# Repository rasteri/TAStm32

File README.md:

# TAStm32
Please see the "Projects" section for an overview of the current status of this project!

Please see the "Wiki" section for the technical details of the serial communication protocol!

### Overview

This project aims to create an easy-to-use, multi-system TAS replay device to be used on actual consoles. The name of this project comes from the fact that it is powered by a STM32F4 microcontroller.

### Prerequisites

First clone or download this repository

#### Get Python3!
Install the [latest Python 3 release](https://www.python.org/downloads/)

(You may need to log out/log in to refresh the PATH variable)

Then install the required python modules with the following command:

    python3 -m pip install -r python/requirements.txt
    
#### Linux users -- make sure you are in the dialout and plugdev groups!
    
### Compilation

#### Linux
    apt install gcc-arm-none-eabi binutils-arm-none-eabi libnewlib-arm-none-eabi
OR the equivalent in your distribution

    make

#### Windows

1. Right-click on the project > Build Configurations > Set Active > Release.
1. Project > Build Project and check that the console shows no errors. The last line before "build finished" should be "arm-atollic-eabi-objcopy -O ihex TAStm32.elf TAStm32.hex".

### Flashing the firmware

#### Linux
    apt install dfu-util
OR the equivalent in your distribution

    make flash

#### Windows
1. Install Atollic TrueStudio
1. Install STM32CubeProgrammer
1. Open up the command prompt
1. Run setenv.bat included in the root directory
1. Run update.bat included in the root directory

### Usage

Dumped TAS movies are available in the [TASBot projects repo](https://github.com/dwangoac/TASBot-Projects/tree/master/replayfiles)

[Scripts to dump your own TASes](https://github.com/dwangoac/TASBot-Projects/blob/master/Dump_Scripts/)

Once you've prepared a movie dump, use it with the TAStm32. Here is one example example is here:

    python3 tastm32.py --console snes --players 1,5 --dpcm --clock 14 --transition 2123 A --blank 1 smb3_agdq.r16m

### Special Thanks
#### TheMas3212 - The main contributor to this project. Aided with all things python, designing the serial communication protocol, helping with PCB design, and debugging throughout the whole process.
#### CraftedCart - Designed the awesome-looking 3D case
#### total (@tewtal) - Helped with NES/SNES protocol and debugging. Provided his code as a reference
#### booto (@booto) - Helped fix N64/GC protocols, serial-over-USB, and debugging

dwangoAC (@dwangoac) - warmly accepting me into the TASBot community

micro500 (@micro500) - spent a lot of time teaching me how console replay devices work at a low level

true - for teaching me hardware concepts, helping me choose the perfect MCU for the job, and explaining a lot of low-level things to me

Tien Majerle (@MaJerle) - the owner of https://stm32f4-discovery.net/ helped me with the function which jumps to the DFU bootloader code

Ilari - for being an extraordinary wealth of knowledge on most topics

Serisium (@serisium) - helped with debugging and PCB design

rcombs (@rcombs) - helped with optimizing the N64 protocol

Sauraen (@sauraen) - Linux setup and installation notes

Derf - worked on debugging the genesis protocol together

#### If I accidentally forgot to credit you, please let me know so I can fix it!

 - Ownasaurus

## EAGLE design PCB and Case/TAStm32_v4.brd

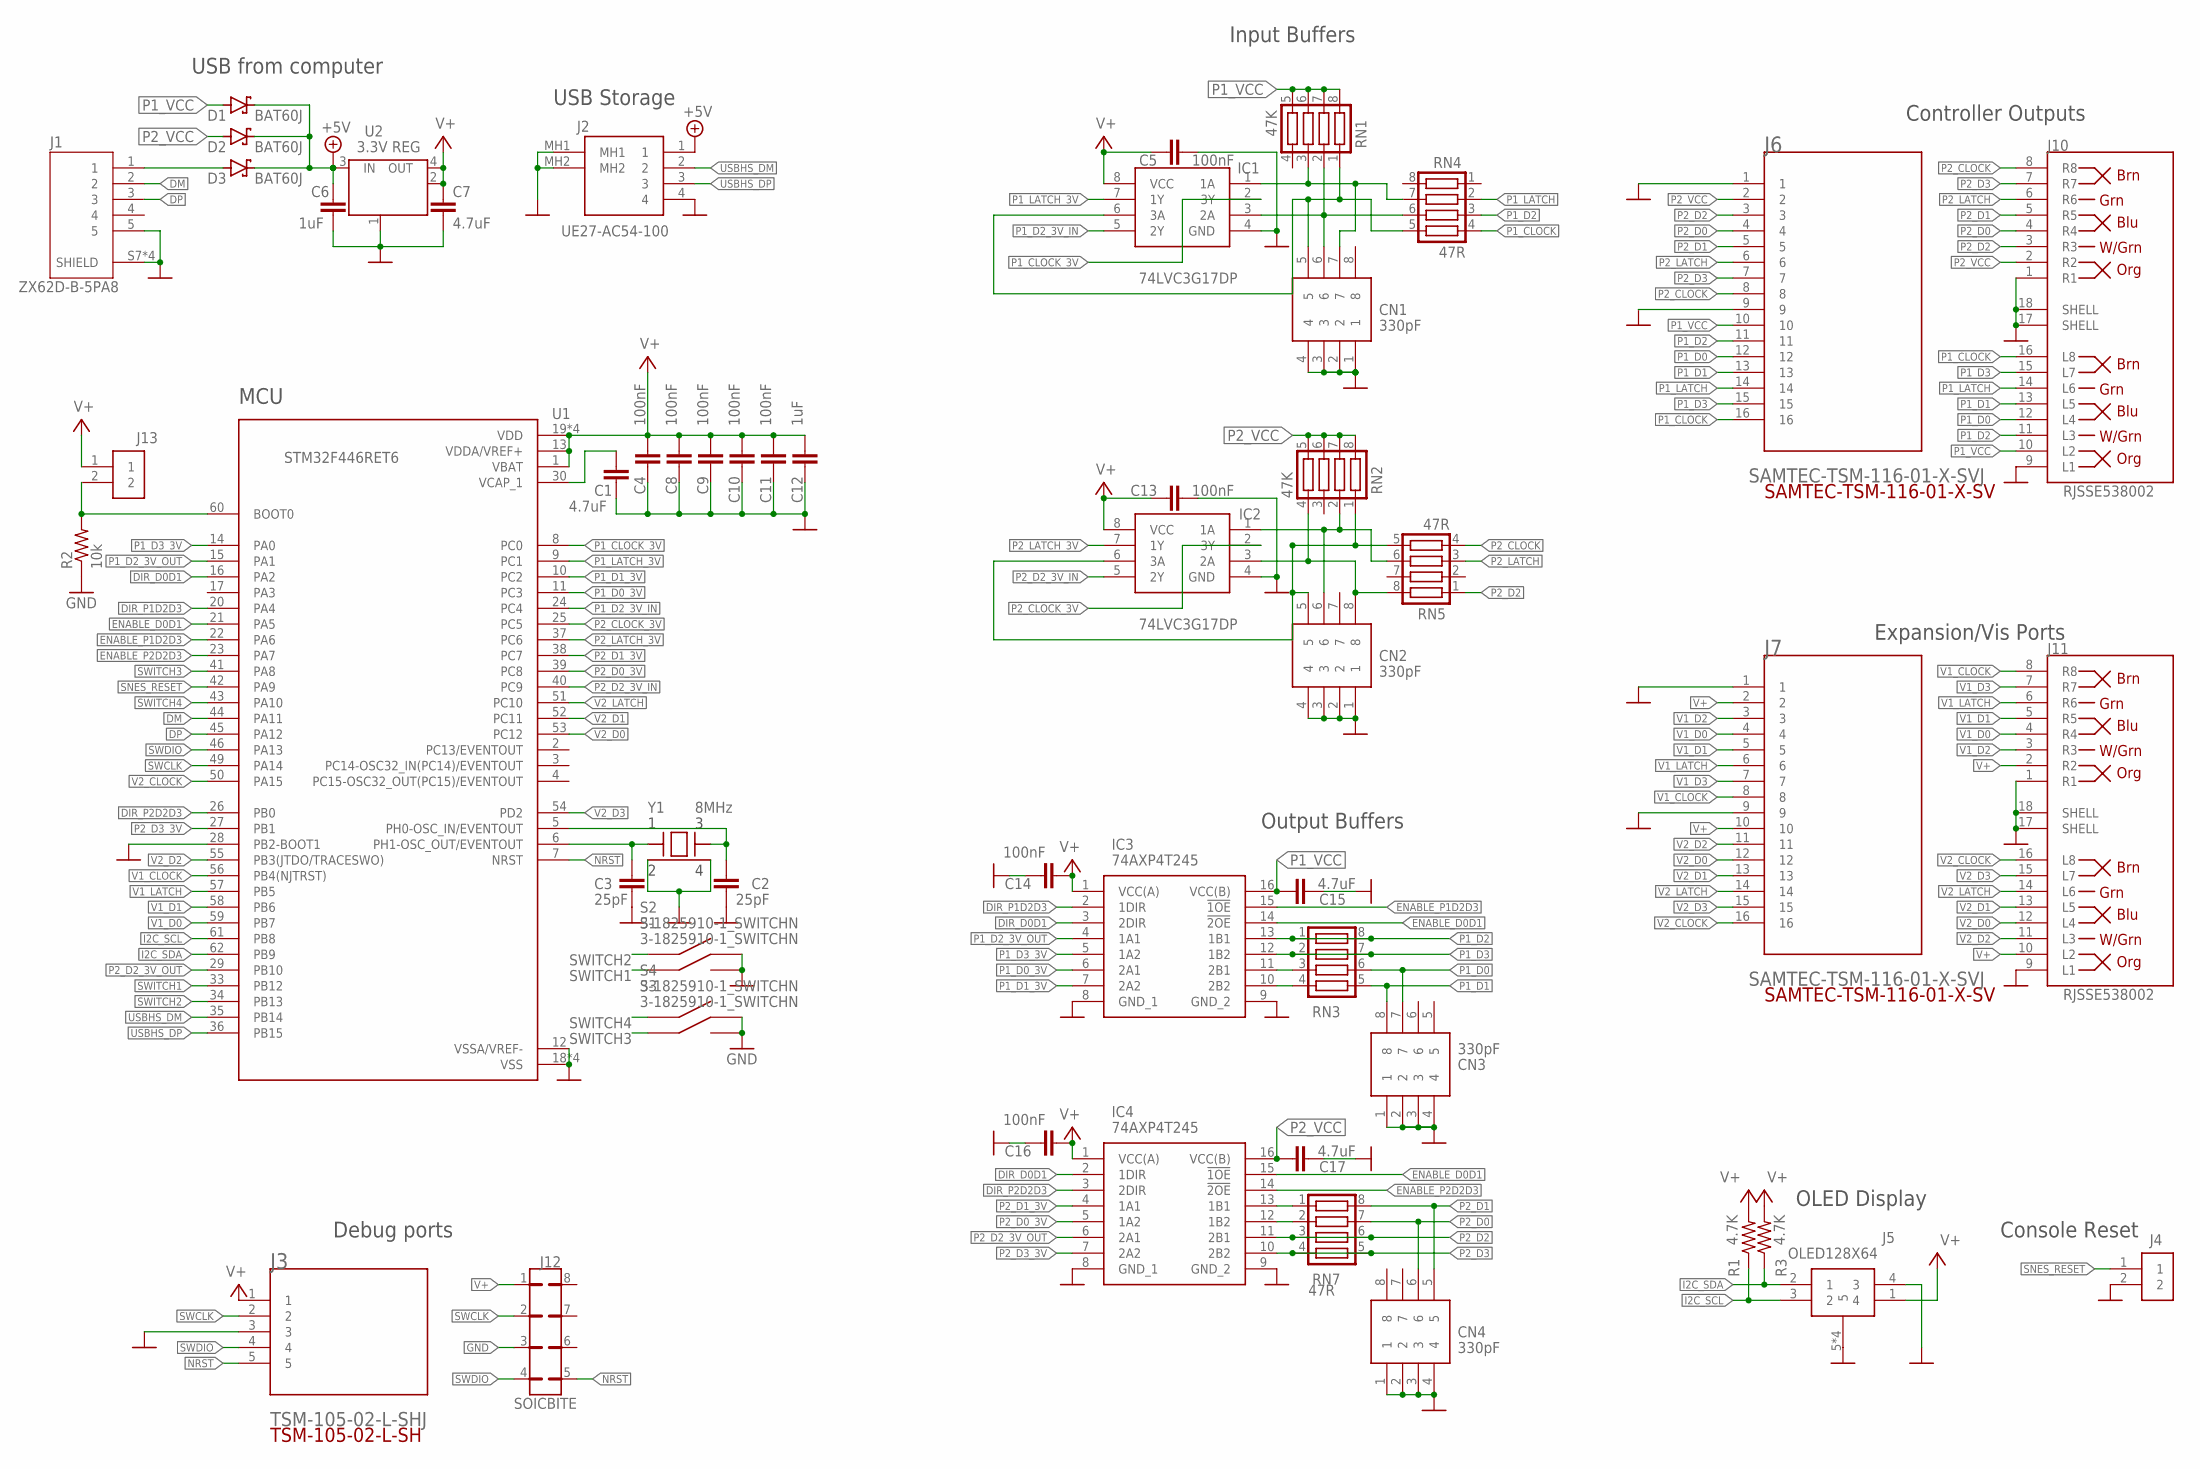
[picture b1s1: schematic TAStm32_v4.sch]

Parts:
C1, C7, C15, C17: 4.7uF; C0603K
C2, C3: 25pF; C0603K
C4, C5, C8, C9, C10, C11, C13, C14, C16: 100nF; C0603K
C6, C12: 1uF; C0603K
CN1, CN2, CN3, CN4: 330pF; CA0612KRX7R7BB104
D1, D2, D3: BAT60J; DIODE_SOD323_ST
IC1, IC2: 74LVC3G17DP; SOP65P400X110-8N
IC3, IC4: 74AXP4T245; SOP65P640X110-16N
J1: ZX62D-B-5PA8; HIROSE_ZX62D-B-5PA8
J2: UE27-AC54-100; UE27AC54100
J3: TSM-105-02-L-SHJ; TSM-105-02-L-SH
J4, J13: CONSOLE_RESET; SAMTEC-TSM-102-01-X-SH
J5: OLED128X64; OLED
J6, J7: SAMTEC-TSM-116-01-X-SVJ; SAMTEC-TSM-116-01-X-SV
J10, J11: RJSSE538002; AMPHENOL_RJSSE538002
J12: SOICBITE
R1, R3: 4.7K; R0805
R2: 10k; R0805
RN1, RN2: 47K; CTS742C083
RN3: CTS742C083
RN4, RN5, RN7: 47R; CTS742C083
S1, S2, S3, S4: 3-1825910-1_SWITCHN; 3-1825910-1_318259101
U1: STM32F446RET6; QFP50P1200X1200X160-64N
U2: 3.3V REG; SOT223
Y1: 8MHz; DFN-4

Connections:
+5V: C6.2, D1.C, D2.C, D3.C, J2.1, U2.3 (IN)
BOOT0: J13.2, R2.2, U1.60 (BOOT0)
DIR_D0D1: IC3.3 (2DIR), IC4.2 (1DIR), U1.16 (PA2)
DIR_P1D2D3: IC3.2 (1DIR), U1.20 (PA4)
DIR_P2D2D3: IC4.3 (2DIR), U1.26 (PB0)
DM: J1.2, U1.44 (PA11)
DP: J1.3, U1.45 (PA12)
ENABLE_D0D1: IC3.14 (!2OE), IC4.15 (!1OE), U1.21 (PA5)
ENABLE_P1D2D3: IC3.15 (!1OE), U1.22 (PA6)
ENABLE_P2D2D3: IC4.14 (!2OE), U1.23 (PA7)
GND: C1.2, C2.1, C3.1, C4.1, C5.2, C6.1, C7.1, C8.1, C9.1, C10.1, C11.1, C12.1, C13.2, C14.1, C15.2, C16.1, C17.2, CN1.1, CN1.2, CN1.3, CN1.4, CN2.1, CN2.2, CN2.3, CN2.4, CN3.1, CN3.2, CN3.3, CN3.4, CN4.1, CN4.2, CN4.3, CN4.4, IC1.4 (GND), IC2.4 (GND), IC3.8 (GND_1), IC3.9 (GND_2), IC4.8 (GND_1), IC4.9 (GND_2), J1.5, J1.S7 (SHIELD), J1.S8 (SHIELD), J1.S9 (SHIELD), J1.S10 (SHIELD), J2.4, J2.MH1, J2.MH2, J3.3, J4.2, J5.4 (3), J5.5, J5.6 (5), J5.7 (5), J5.8 (5), J6.1, J6.9, J7.1, J7.9, J10.1 (R1), J10.9 (L1), J10.17 (SHELL), J10.18 (SHELL), J11.1 (R1), J11.9 (L1), J11.17 (SHELL), J11.18 (SHELL), J12.3, R2.1, S1.3, S1.4, S2.3, S2.4, S3.3, S3.4, S4.3, S4.4, U1.12 (VSSA/VREF-), U1.18 (VSS), U1.28 (PB2-BOOT1), U1.31 (VSS), U1.47 (VSS), U1.63 (VSS), U2.1 (GND/ADJ), Y1.2, Y1.4
I2C_SCL: J5.3 (2), R1.1, U1.61 (PB8)
I2C_SDA: J5.2 (1), R3.1, U1.62 (PB9)
unnamed: D3.A, J1.1
unnamed: CN2.6, IC2.1 (1A), RN2.2, RN5.6
unnamed: C3.2, U1.6 (PH1-OSC_OUT/EVENTOUT), Y1.1
unnamed: CN2.5, IC2.6 (3A), RN2.1, RN5.5
unnamed: CN2.8, IC2.3 (2A), RN2.4, RN5.8
unnamed: IC3.11 (2B1), RN3.3
unnamed: IC3.10 (2B2), RN3.4
unnamed: IC4.12 (1B2), RN7.2
unnamed: IC4.13 (1B1), RN7.1
unnamed: CN1.7, IC1.1 (1A), RN1.3, RN4.7
unnamed: CN1.5, IC1.6 (3A), RN1.1, RN4.5
unnamed: CN1.6, IC1.3 (2A), RN1.2, RN4.6
NRST: J3.5, J12.5, U1.7 (NRST)
P1_CLOCK: J6.16, J10.16 (L8), RN4.4
P1_CLOCK_3V: IC1.2 (3Y), U1.8 (PC0)
P1_D0: CN3.7, J6.12, J10.12 (L4), RN3.6
P1_D0_3V: IC3.6 (2A1), U1.11 (PC3)
P1_D1: CN3.8, J6.13, J10.13 (L5), RN3.5
P1_D1_3V: IC3.7 (2A2), U1.10 (PC2)
P1_D2: IC3.13 (1B1), J6.11, J10.11 (L3), RN3.1, RN3.8, RN4.3
P1_D2_3V_IN: IC1.5 (2Y), U1.24 (PC4)
P1_D2_3V_OUT: IC3.4 (1A1), U1.15 (PA1)
P1_D3: IC3.12 (1B2), J6.15, J10.15 (L7), RN3.2, RN3.7
P1_D3_3V: IC3.5 (1A2), U1.14 (PA0)
P1_LATCH: J6.14, J10.14 (L6), RN4.2
P1_LATCH_3V: IC1.7 (1Y), U1.9 (PC1)
P1_VCC: C15.1, D1.A, IC3.16 (VCC(B)), J6.10, J10.10 (L2), RN1.5, RN1.6, RN1.7, RN1.8
P2_CLOCK: J6.8, J10.8 (R8), RN5.4
P2_CLOCK_3V: IC2.2 (3Y), U1.25 (PC5)
P2_D0: CN4.6, J6.4, J10.4 (R4), RN7.7
P2_D0_3V: IC4.5 (1A2), U1.39 (PC8)
P2_D1: CN4.5, J6.5, J10.5 (R5), RN7.8
P2_D1_3V: IC4.4 (1A1), U1.38 (PC7)
P2_D2: IC4.11 (2B1), J6.3, J10.3 (R3), RN5.1, RN7.3, RN7.6
P2_D2_3V_IN: IC2.5 (2Y), U1.40 (PC9)
P2_D2_3V_OUT: IC4.6 (2A1), U1.29 (PB10)
P2_D3: IC4.10 (2B2), J6.7, J10.7 (R7), RN7.4, RN7.5
P2_D3_3V: IC4.7 (2A2), U1.27 (PB1)
P2_LATCH: J6.6, J10.6 (R6), RN5.3
P2_LATCH_3V: IC2.7 (1Y), U1.37 (PC6)
P2_VCC: C17.1, D2.A, IC4.16 (VCC(B)), J6.2, J10.2 (R2), RN2.5, RN2.6, RN2.7, RN2.8
SNES_RESET: J4.1, U1.42 (PA9)
SWCLK: J3.2, J12.2, U1.49 (PA14)
SWDIO: J3.4, J12.4, U1.46 (PA13)
SWITCH1: S1.1, S1.2, U1.33 (PB12)
SWITCH2: S2.1, S2.2, U1.34 (PB13)
SWITCH3: S3.1, S3.2, U1.41 (PA8)
SWITCH4: S4.1, S4.2, U1.43 (PA10)
USBHS_DM: J2.2, U1.35 (PB14)
USBHS_DP: J2.3, U1.36 (PB15)
V1_CLOCK: J7.8, J11.8 (R8), U1.56 (PB4(NJTRST))
V1_D0: J7.4, J11.4 (R4), U1.59 (PB7)
V1_D1: J7.5, J11.5 (R5), U1.58 (PB6)
V1_D2: J7.3, J11.3 (R3)
V1_D3: J7.7, J11.7 (R7)
V1_LATCH: J7.6, J11.6 (R6), U1.57 (PB5)
V2_CLOCK: J7.16, J11.16 (L8), U1.50 (PA15)
V2_D0: J7.12, J11.12 (L4), U1.53 (PC12)
V2_D1: J7.13, J11.13 (L5), U1.52 (PC11)
V2_D2: J7.11, J11.11 (L3), U1.55 (PB3(JTDO/TRACESWO))
V2_D3: J7.15, J11.15 (L7), U1.54 (PD2)
V2_LATCH: J7.14, J11.14 (L6), U1.51 (PC10)
V+: C4.2, C5.1, C7.2, C8.2, C9.2, C10.2, C11.2, C12.2, C13.1, C14.2, C16.2, IC1.8 (VCC), IC2.8 (VCC), IC3.1 (VCC(A)), IC4.1 (VCC(A)), J3.1, J5.1 (4), J7.2, J7.10, J11.2 (R2), J11.10 (L2), J12.1, J13.1, R1.2, R3.2, U1.1 (VBAT), U1.13 (VDDA/VREF+), U1.19 (VDD), U1.32 (VDD), U1.48 (VDD), U1.64 (VDD), U2.2 (OUT), U2.4 (OUT)
VCAP: C1.1, U1.30 (VCAP_1)
XTAL1: C2.2, U1.5 (PH0-OSC_IN/EVENTOUT), Y1.3

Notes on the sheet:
USB from computer
USB Storage
MCU
Debug ports
OLED Display
Console Reset
Controller Outputs
Expansion/Vis Ports
Input Buffers
Output Buffers

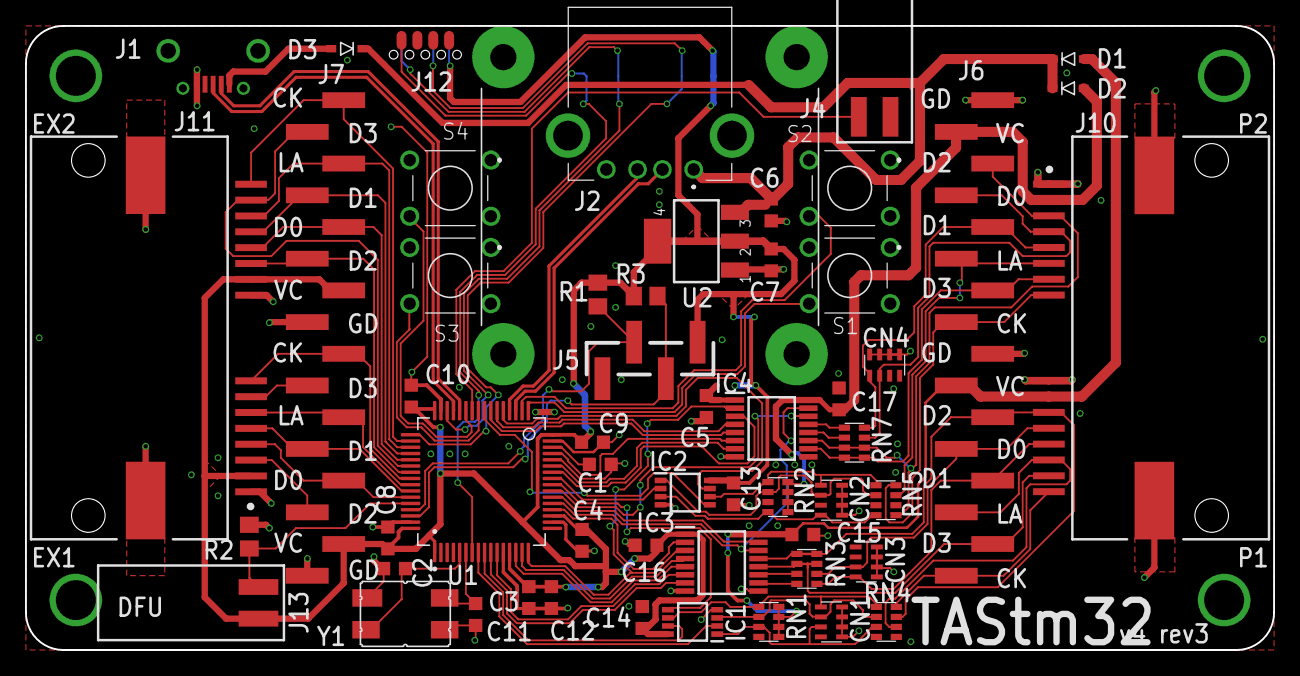
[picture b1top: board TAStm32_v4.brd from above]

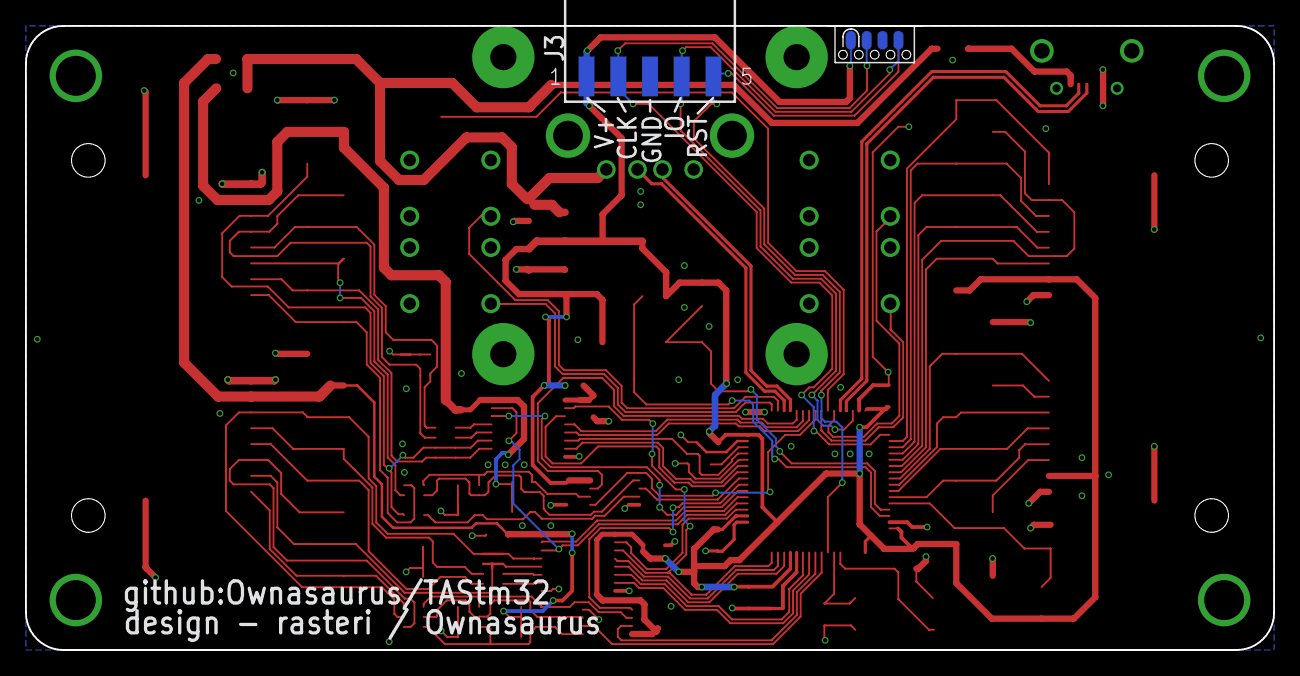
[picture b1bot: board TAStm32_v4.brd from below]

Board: 2 copper layers, 100.0 x 50.0 mm, 55 parts (2 on the bottom side), 78 nets.

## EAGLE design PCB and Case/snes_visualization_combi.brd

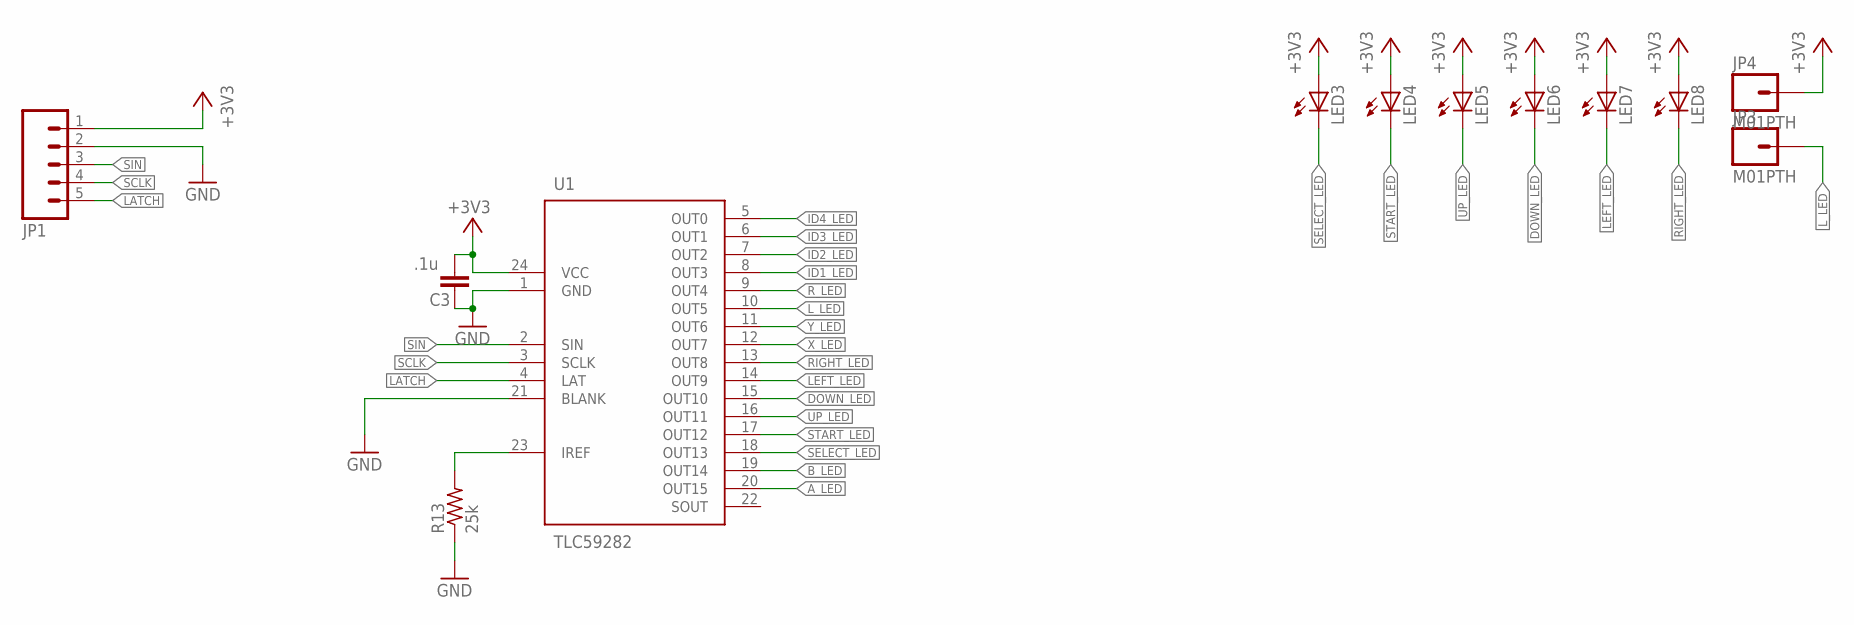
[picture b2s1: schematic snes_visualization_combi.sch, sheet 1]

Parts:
C3: .1u; C0603; MOUSER# 80-C0603C104K5R
JP1: M05PTH; 1X05
JP3, JP4: M01PTH; 1X01
LED3, LED4: LED3MM
LED5, LED6, LED7, LED8: LED5MM
R13: 25k; R0805
U1: TLC59282; R-PDSO-G24

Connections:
+3V3: C3.1, JP1.1, JP4.1, LED3.A, LED4.A, LED5.A, LED6.A, LED7.A, LED8.A, U1.24 (VCC); also elsewhere on the board
A_LED: U1.20 (OUT15); also elsewhere on the board
B_LED: U1.19 (OUT14); also elsewhere on the board
DOWN_LED: LED6.K (C), U1.15 (OUT10)
GND: C3.2, JP1.2, R13.1, U1.1 (GND), U1.21 (BLANK)
ID1_LED: U1.8 (OUT3); also elsewhere on the board
ID2_LED: U1.7 (OUT2); also elsewhere on the board
ID3_LED: U1.6 (OUT1); also elsewhere on the board
ID4_LED: U1.5 (OUT0); also elsewhere on the board
LATCH: JP1.5, U1.4 (LAT)
LEFT_LED: LED7.K (C), U1.14 (OUT9)
L_LED: JP3.1, U1.10 (OUT5)
unnamed: R13.2, U1.23 (IREF)
RIGHT_LED: LED8.K (C), U1.13 (OUT8)
R_LED: U1.9 (OUT4); also elsewhere on the board
SCLK: JP1.4, U1.3 (SCLK)
SELECT_LED: LED3.K (C), U1.18 (OUT13)
SIN: JP1.3, U1.2 (SIN)
START_LED: LED4.K (C), U1.17 (OUT12)
UP_LED: LED5.K (C), U1.16 (OUT11)
X_LED: U1.12 (OUT7); also elsewhere on the board
Y_LED: U1.11 (OUT6); also elsewhere on the board

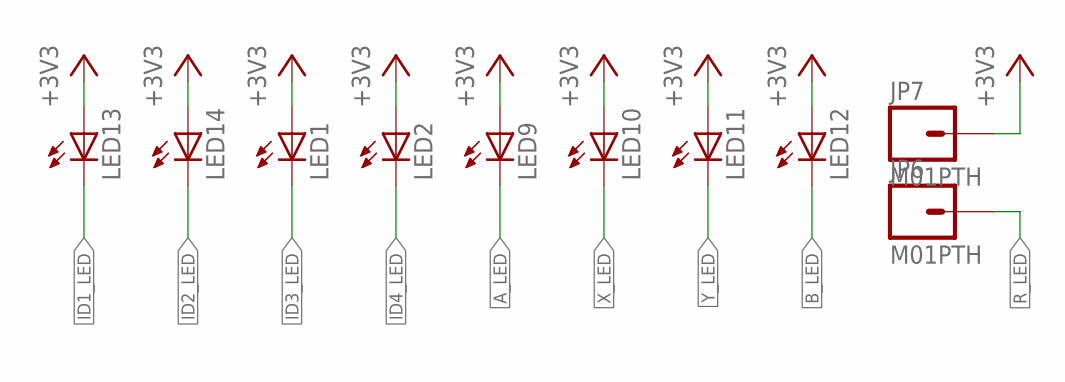
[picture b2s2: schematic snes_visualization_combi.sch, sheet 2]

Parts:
JP6, JP7: M01PTH; 1X01
LED1, LED2, LED9, LED10, LED11, LED12, LED13, LED14: LED5MM

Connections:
+3V3: JP7.1, LED1.A, LED2.A, LED9.A, LED10.A, LED11.A, LED12.A, LED13.A, LED14.A; also elsewhere on the board
A_LED: LED9.K (C); also elsewhere on the board
B_LED: LED12.K (C); also elsewhere on the board
ID1_LED: LED13.K (C); also elsewhere on the board
ID2_LED: LED14.K (C); also elsewhere on the board
ID3_LED: LED1.K (C); also elsewhere on the board
ID4_LED: LED2.K (C); also elsewhere on the board
R_LED: JP6.1; also elsewhere on the board
X_LED: LED10.K (C); also elsewhere on the board
Y_LED: LED11.K (C); also elsewhere on the board

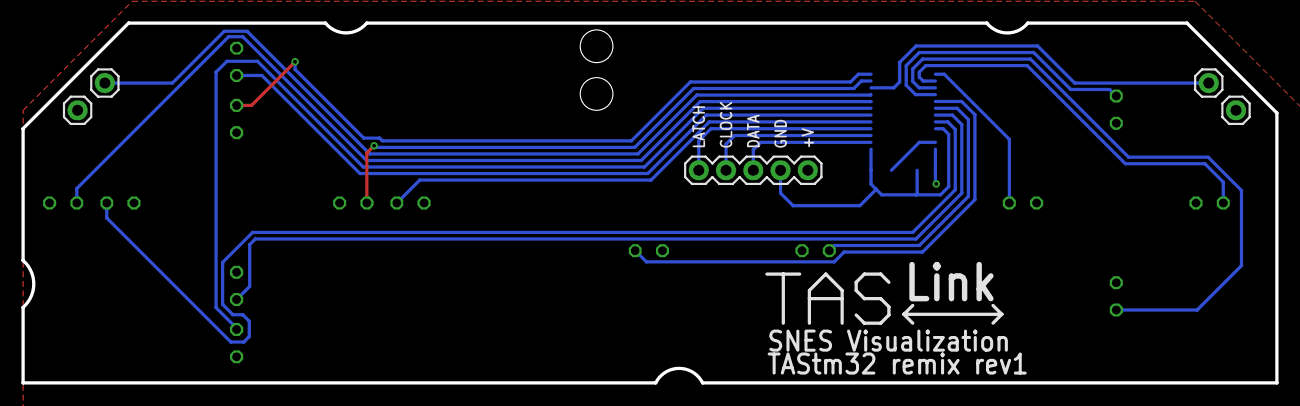
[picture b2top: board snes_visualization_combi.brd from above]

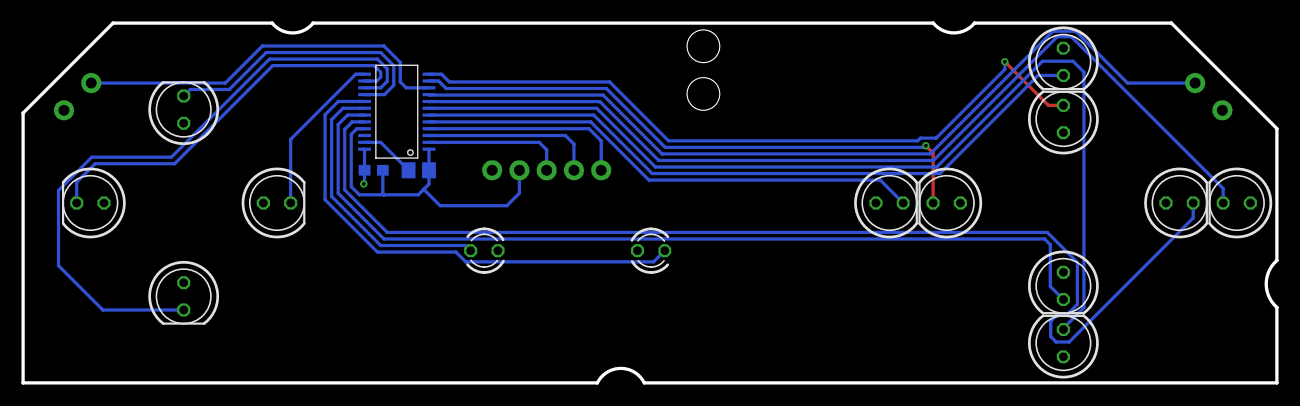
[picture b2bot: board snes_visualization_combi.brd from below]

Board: 2 copper layers, 116.8 x 33.5 mm, 22 parts (17 on the bottom side), 22 nets.

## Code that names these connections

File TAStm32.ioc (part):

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Mcu.Name=STM32F446R(C-E)Tx
Mcu.Package=LQFP64
Mcu.UserName=STM32F446RETx
PA0-WKUP.GPIOParameters=GPIO_Speed,GPIO_Label
PA0-WKUP.GPIO_Label=P1_DATA_3
PA0-WKUP.GPIO_Speed=GPIO_SPEED_FREQ_MEDIUM
PA0-WKUP.Signal=GPIO_Output
PA1.GPIOParameters=GPIO_PuPd,GPIO_Label
PA1.GPIO_Label=P1_DATA_2_OUT
PA1.GPIO_PuPd=GPIO_PULLUP
PA1.Signal=GPIO_Input
PA10.GPIOParameters=GPIO_Label
PA10.GPIO_Label=SWITCH4
PA10.Signal=GPIO_Input
PA11.Mode=Device_Only
PA11.Signal=USB_OTG_FS_DM
PA12.Mode=Device_Only
PA12.Signal=USB_OTG_FS_DP
PA13.GPIOParameters=GPIO_Label
PA13.GPIO_Label=TMS
PA13.Mode=Serial_Wire
PA13.Signal=SYS_JTMS-SWDIO
PA14.GPIOParameters=GPIO_Label
PA14.GPIO_Label=TCK
PA14.Mode=Serial_Wire
PA14.Signal=SYS_JTCK-SWCLK
PA15.GPIOParameters=GPIO_Speed,PinState,GPIO_Label
PA15.GPIO_Label=V2_CLOCK
PA15.GPIO_Speed=GPIO_SPEED_FREQ_VERY_HIGH
PA15.PinState=GPIO_PIN_RESET
PA15.Signal=GPIO_Output
PA2.GPIOParameters=GPIO_Speed,PinState,GPIO_Label
PA2.GPIO_Label=DIR_D0D1
PA2.GPIO_Speed=GPIO_SPEED_FREQ_MEDIUM
PA2.PinState=GPIO_PIN_SET
PA2.Signal=GPIO_Output
PA3.GPIOParameters=GPIO_PuPd,GPIO_Label
PA3.GPIO_Label=PA3
PA3.GPIO_PuPd=GPIO_PULLUP
PA3.Signal=GPIO_Input
PA4.GPIOParameters=GPIO_Speed,PinState,GPIO_Label
PA4.GPIO_Label=DIR_P1D2D3
PA4.GPIO_Speed=GPIO_SPEED_FREQ_MEDIUM
PA4.PinState=GPIO_PIN_SET
PA4.Signal=GPIO_Output
PA5.GPIOParameters=GPIO_Speed,PinState,GPIO_Label
PA5.GPIO_Label=ENABLE_D0D1
PA5.GPIO_Speed=GPIO_SPEED_FREQ_MEDIUM
PA5.PinState=GPIO_PIN_SET
PA5.Signal=GPIO_Output
PA6.GPIOParameters=GPIO_Speed,PinState,GPIO_Label
PA6.GPIO_Label=ENABLE_P1D2D3
PA6.GPIO_Speed=GPIO_SPEED_FREQ_MEDIUM
PA6.PinState=GPIO_PIN_SET
PA6.Signal=GPIO_Output
PA7.GPIOParameters=GPIO_Speed,PinState,GPIO_Label
PA7.GPIO_Label=ENABLE_P2D2D3
PA7.GPIO_Speed=GPIO_SPEED_FREQ_MEDIUM
PA7.PinState=GPIO_PIN_SET
PA7.Signal=GPIO_Output
PA8.GPIOParameters=GPIO_PuPd,GPIO_Label
PA8.GPIO_Label=SWITCH3
PA8.GPIO_PuPd=GPIO_PULLUP
PA8.Signal=GPIO_Input
PA9.GPIOParameters=GPIO_Speed,GPIO_Label
PA9.GPIO_Label=SNES_RESET
PA9.GPIO_Speed=GPIO_SPEED_FREQ_MEDIUM
PA9.Signal=GPIO_Output
PB0.GPIOParameters=GPIO_Speed,GPIO_Label
PB0.GPIO_Label=DIR_P2D2D3
PB0.GPIO_Speed=GPIO_SPEED_FREQ_MEDIUM
PB0.Signal=GPIO_Output
PB1.GPIOParameters=GPIO_Label
PB1.GPIO_Label=P2_DATA_3
PB1.Signal=GPIO_Output
PB10.GPIOParameters=GPIO_Speed,GPIO_Label
PB10.GPIO_Label=P2_DATA_2_OUT
PB10.GPIO_Speed=GPIO_SPEED_FREQ_MEDIUM
PB10.Signal=GPIO_Output
PB12.GPIOParameters=GPIO_PuPd,GPIO_Label
PB12.GPIO_Label=SWITCH1
PB12.GPIO_PuPd=GPIO_PULLUP
PB12.Signal=GPIO_Input
PB13.GPIOParameters=GPIO_PuPd,GPIO_Label
PB13.GPIO_Label=SWITCH2
PB13.GPIO_PuPd=GPIO_PULLUP
PB13.Signal=GPIO_Input
PB14.Mode=Host_FS
PB14.Signal=USB_OTG_HS_DM
PB15.Mode=Host_FS
PB15.Signal=USB_OTG_HS_DP
PB3.GPIOParameters=GPIO_Label
PB3.GPIO_Label=V1_DATA_2
PB3.Signal=GPIO_Output
PB4.GPIOParameters=GPIO_Speed,PinState,GPIO_Label
PB4.GPIO_Label=V1_CLOCK
PB4.GPIO_Speed=GPIO_SPEED_FREQ_VERY_HIGH
PB4.PinState=GPIO_PIN_RESET
PB4.Signal=GPIO_Output
PB5.GPIOParameters=GPIO_Speed,GPIO_Label
PB5.GPIO_Label=V1_LATCH
PB5.GPIO_Speed=GPIO_SPEED_FREQ_VERY_HIGH
PB5.Signal=GPIO_Output
PB6.GPIOParameters=GPIO_Speed,PinState,GPIO_Label
PB6.GPIO_Label=V1_DATA_1
PB6.GPIO_Speed=GPIO_SPEED_FREQ_VERY_HIGH
PB6.PinState=GPIO_PIN_RESET
PB6.Signal=GPIO_Output
PB7.GPIOParameters=GPIO_Speed,PinState,GPIO_Label
PB7.GPIO_Label=V1_DATA_0
PB7.GPIO_Speed=GPIO_SPEED_FREQ_VERY_HIGH
PB7.PinState=GPIO_PIN_RESET
PB7.Signal=GPIO_Output
PB8.Mode=I2C
PB8.Signal=I2C1_SCL
PB9.Mode=I2C
PB9.Signal=I2C1_SDA
PC0.GPIOParameters=GPIO_PuPd,GPIO_Label
PC0.GPIO_Label=P1_CLOCK
PC0.GPIO_PuPd=GPIO_PULLDOWN
PC0.Signal=GPXTI0
PC1.GPIOParameters=GPIO_PuPd,GPIO_Label
PC1.GPIO_Label=P1_LATCH
PC1.GPIO_PuPd=GPIO_PULLDOWN
PC1.Signal=GPXTI1
PC10.GPIOParameters=GPIO_Speed,PinState,GPIO_Label
PC10.GPIO_Label=V2_LATCH
PC10.GPIO_Speed=GPIO_SPEED_FREQ_VERY_HIGH
PC10.PinState=GPIO_PIN_RESET
PC10.Signal=GPIO_Output
PC11.GPIOParameters=GPIO_Speed,PinState,GPIO_Label
PC11.GPIO_Label=V2_DATA_1
PC11.GPIO_Speed=GPIO_SPEED_FREQ_VERY_HIGH
PC11.PinState=GPIO_PIN_RESET
PC11.Signal=GPIO_Output
PC12.GPIOParameters=GPIO_Speed,PinState,GPIO_Label
PC12.GPIO_Label=V2_DATA_0
PC12.GPIO_Speed=GPIO_SPEED_FREQ_VERY_HIGH
PC12.PinState=GPIO_PIN_RESET
PC12.Signal=GPIO_Output
PC13.GPIOParameters=GPIO_PuPd,GPIO_Label
PC13.GPIO_Label=PC13
PC13.GPIO_PuPd=GPIO_PULLUP
PC13.Signal=GPIO_Input
PC14-OSC32_IN.GPIOParameters=GPIO_PuPd,GPIO_Label
PC14-OSC32_IN.GPIO_Label=PC14
PC14-OSC32_IN.GPIO_PuPd=GPIO_PULLUP
PC14-OSC32_IN.Signal=GPIO_Input
PC15-OSC32_OUT.GPIOParameters=GPIO_Label
PC15-OSC32_OUT.GPIO_Label=PC15
PC15-OSC32_OUT.Signal=GPIO_Output
PC2.GPIOParameters=GPIO_PuPd,GPIO_Label
PC2.GPIO_Label=P1_DATA_1
PC2.GPIO_PuPd=GPIO_PULLDOWN
PC2.Signal=GPIO_Input
PC3.GPIOParameters=GPIO_PuPd,GPIO_Label
PC3.GPIO_Label=P1_DATA_0
PC3.GPIO_PuPd=GPIO_PULLDOWN
PC3.Signal=GPIO_Input
PC4.GPIOParameters=GPIO_PuPd,GPIO_Label,GPIO_ModeDefaultEXTI
PC4.GPIO_Label=P1_DATA_2
PC4.GPIO_ModeDefaultEXTI=GPIO_MODE_IT_FALLING
PC4.GPIO_PuPd=GPIO_PULLDOWN
PC4.Signal=GPXTI4
PC5.GPIOParameters=GPIO_PuPd,GPIO_Label
PC5.GPIO_Label=P2_CLOCK
PC5.GPIO_PuPd=GPIO_PULLDOWN
PC5.Signal=GPXTI5
PC6.GPIOParameters=GPIO_PuPd,GPIO_Label
PC6.GPIO_Label=P2_LATCH
PC6.GPIO_PuPd=GPIO_PULLDOWN
PC6.Signal=GPIO_Input
PC7.GPIOParameters=GPIO_PuPd,GPIO_Label
PC7.GPIO_Label=P2_DATA_1
PC7.GPIO_PuPd=GPIO_PULLDOWN
PC7.Signal=GPIO_Input
PC8.GPIOParameters=GPIO_PuPd,GPIO_Label
PC8.GPIO_Label=P2_DATA_0
PC8.GPIO_PuPd=GPIO_PULLDOWN
PC8.Signal=GPIO_Input
PC9.GPIOParameters=GPIO_PuPd,GPIO_Label
PC9.GPIO_Label=P2_DATA_2
PC9.GPIO_PuPd=GPIO_PULLDOWN
PC9.Signal=GPIO_Input
PD2.GPIOParameters=GPIO_Label
PD2.GPIO_Label=V2_DATA_3
PD2.Signal=GPIO_Output
PH0-OSC_IN.Mode=HSE-External-Oscillator
PH0-OSC_IN.Signal=RCC_OSC_IN
PH1-OSC_OUT.Mode=HSE-External-Oscillator
PH1-OSC_OUT.Signal=RCC_OSC_OUT
RCC.HSE_VALUE=8000000
RCC.SYSCLKFreq_VALUE=168000000
RCC.SYSCLKSource=RCC_SYSCLKSOURCE_PLLCLK
board=NUCLEO-F446RE
boardIOC=true

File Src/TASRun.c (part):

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	SetupPin(GPIOC, 0xFFCF, GPIO_MODE_INPUT, GPIO_PULLUP, GPIO_PIN_RESET);

	// Switches, input pullup (expressly done here so we can easily switch above to pulldowns if needed)
	SetupPin(SWITCH1_GPIO_Port, SWITCH1_Pin, GPIO_MODE_INPUT, GPIO_PULLUP, GPIO_PIN_SET);
	SetupPin(SWITCH2_GPIO_Port, SWITCH2_Pin, GPIO_MODE_INPUT, GPIO_PULLUP, GPIO_PIN_SET);
	SetupPin(SWITCH3_GPIO_Port, SWITCH3_Pin, GPIO_MODE_INPUT, GPIO_PULLUP, GPIO_PIN_SET);
	SetupPin(SWITCH4_GPIO_Port, SWITCH4_Pin, GPIO_MODE_INPUT, GPIO_PULLUP, GPIO_PIN_SET);

	// tristate all external buffers on v4 board (i.e. set their enable pins high)
	#ifdef BOARDV4
	SetupPin(ENABLE_D0D1_GPIO_Port, ENABLE_D0D1_Pin, GPIO_MODE_OUTPUT_PP, GPIO_NOPULL, GPIO_PIN_SET);
	SetupPin(ENABLE_P1D2D3_GPIO_Port, ENABLE_P1D2D3_Pin, GPIO_MODE_OUTPUT_PP, GPIO_NOPULL, GPIO_PIN_SET);
	SetupPin(ENABLE_P2D2D3_GPIO_Port, ENABLE_P2D2D3_Pin, GPIO_MODE_OUTPUT_PP, GPIO_NOPULL, GPIO_PIN_SET);
	#endif
}

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	// clear all interrupts
	while (HAL_NVIC_GetPendingIRQ(EXTI0_IRQn))
	{
		__HAL_GPIO_EXTI_CLEAR_IT(P1_CLOCK_Pin);
		HAL_NVIC_ClearPendingIRQ(EXTI0_IRQn);
	}
	while (HAL_NVIC_GetPendingIRQ(EXTI1_IRQn))
	{
		__HAL_GPIO_EXTI_CLEAR_IT(P1_LATCH_Pin);
		HAL_NVIC_ClearPendingIRQ(EXTI1_IRQn);
	}
	while (HAL_NVIC_GetPendingIRQ(EXTI4_IRQn))
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	}
	while (HAL_NVIC_GetPendingIRQ(EXTI9_5_IRQn))
	{
		__HAL_GPIO_EXTI_CLEAR_IT(P2_CLOCK_Pin);
		HAL_NVIC_ClearPendingIRQ(EXTI9_5_IRQn);
	}
	while (HAL_NVIC_GetPendingIRQ(TIM3_IRQn))
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	//HAL_GPIO_WritePin(DIR_P1P2D2D3_GPIO_Port, DIR_P1P2D2D3_Pin, GPIO_PIN_RESET);

	// Buffer Enable P1D2
	//HAL_GPIO_WritePin(ENABLE_P1D2D3_GPIO_Port, ENABLE_P1D2D3_Pin, GPIO_PIN_RESET);

	// MCU P1D2 input, triggered on falling edge
	SetupPin(P1_DATA_2_GPIO_Port, P1_DATA_2_Pin, GPIO_MODE_IT_FALLING, GPIO_NOPULL, GPIO_PIN_RESET);
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	#ifdef BOARDV4
	// external output buffers should already be tristated, so set direction to output (i.e. high)
	// Buffer will be enabled on first latch
	SetupPin(DIR_D0D1_GPIO_Port, DIR_D0D1_Pin, GPIO_MODE_OUTPUT_PP, GPIO_NOPULL, GPIO_PIN_SET);
	SetupPin(DIR_P1D2D3_GPIO_Port, DIR_P1D2D3_Pin, GPIO_MODE_OUTPUT_PP, GPIO_NOPULL, GPIO_PIN_SET);
	SetupPin(DIR_P2D2D3_GPIO_Port, DIR_P2D2D3_Pin, GPIO_MODE_OUTPUT_PP, GPIO_NOPULL, GPIO_PIN_SET);

	// Now do the actual MCU pins
	// MCU D0/D1/D2/D3 output, but they will not actually speak to console yet as buffer is disabled
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	#endif //BOARDV4

	// MCU Clock/latch input, triggered on rising edge
	SetupPin(GPIOC, P1_CLOCK_Pin|P1_LATCH_Pin|P2_CLOCK_Pin, GPIO_MODE_IT_RISING, GPIO_NOPULL, GPIO_PIN_RESET);
}

void SetSNESMode()
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	#ifdef BOARDV4
	// external output buffers should already be tristated, so set direction to output (i.e. high)
	// Buffer will be enabled on first latch
	SetupPin(DIR_D0D1_GPIO_Port, DIR_D0D1_Pin, GPIO_MODE_OUTPUT_PP, GPIO_NOPULL, GPIO_PIN_SET);
	// D2 buffers should be input - so taken care of by the input buffers, which are always enabled

	// Now do the actual MCU pins
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	#endif //BOARDV3

	// MCU Clock/latch input, triggered on rising edge
	SetupPin(GPIOC, P1_CLOCK_Pin|P1_LATCH_Pin|P2_CLOCK_Pin, GPIO_MODE_IT_RISING, GPIO_NOPULL, GPIO_PIN_RESET);
}

void SetGENMode()
{
	GPIO_InitTypeDef GPIO_InitStruct = {0};

	// P1_D0 --> GEN Pin 1
	// P1_D1 --> GEN Pin 2
	// P1_D2 --> GEN Pin 3
	// P2_D0 --> GEN Pin 4
	// P2_D1 --> GEN Pin 6
	// P2_D2 --> GEN Pin 9

	// Ensure the latch pin interrupts on BOTH rising and falling. use this as the select line
	GPIO_InitStruct.Pin = P1_LATCH_Pin;
	GPIO_InitStruct.Mode = GPIO_MODE_IT_RISING_FALLING;
	GPIO_InitStruct.Pull = GPIO_PULLUP;

	HAL_GPIO_Init(P1_LATCH_GPIO_Port, &GPIO_InitStruct);

	memset (&GPIO_InitStruct, 0, sizeof(GPIO_InitTypeDef));

	// Tristate the data pins until the first latch
	GPIO_InitStruct.Pin = P1_DATA_0_Pin | P1_DATA_1_Pin | P1_DATA_2_Pin  | P2_DATA_0_Pin | P2_DATA_1_Pin | P2_DATA_2_Pin;
	GPIO_InitStruct.Mode = GPIO_MODE_INPUT;
	HAL_GPIO_Init(GPIOC, &GPIO_InitStruct);
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
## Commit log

2020-02-17 WIP json settings file
    --save <file> to store setting to file
    --load <file> to load settings from file
    --nomovie to skip storing movie information in file
2020-03-02 wip2
2020-03-28 Dev work for cli version
2020-03-28 more WIP
2020-03-28 Handle crash on runs that are smaller than buffer (line 225), fix typo on line 276, fix crash when no transitions defined (line 232)
2020-03-28 further progress on add command
2020-03-28 Fix Debug flag
2020-03-28 changed some of the code organization; dumped in do_new which needs to be edited to work
2020-03-28 fix ++
2020-03-28 started basic cli framework
2020-03-28 Break on end of last Run
2020-03-29 converted macro to inline function; begin re-organizing init code
2020-03-30 revised code to prepare first frame
2020-04-07 - test negative blank frame count
2020-05-01 Fix space != tab in Makefile
2020-06-04 genesis framework in place except for timer. untested.
2020-06-05 added timer config for GEN. testing still needed
2020-06-06 fixed bugs in timer, communication, and python; still not yet working
2020-06-06 fixed interrupt priority and gmv bit polarity
2020-06-06 - Repack genesis input data in python loader
2020-06-06 - Slight change to controller byte settings for Genesis
2020-06-06 - Fix typo in gmv.py
2020-06-06 - Fix blankframe logic for Genesis
2020-06-06 py improvements. testing code
2020-06-06 hopefuly some improvements? but its too slow!
2020-06-08 - Replace gmv parser with rgen parser due to lagframes
2020-06-09 somewhat works!
2020-06-10 functional 3 button. fixed poweron issue
2020-06-23 fixing some nes/snes bugs
2020-06-24 dont know why runs bug sometimes
2020-08-27 - Basic timing implementation
2020-08-27 - Also work in Bulk transfer mode
2020-09-06 first test candidate for midi n64 drums
2020-09-06 update Requirements.txt for midi modules
2020-09-11 update pinmap comments
2020-10-23 new graphics
2020-10-23 new gfx
2020-10-23 even more new gfx
2020-10-24 gfx tweaks
2020-10-27 Better D-PAD graphics
2020-10-27 left dpad graphic
2020-10-27 taspad stuff
2020-10-31 taspad works now
2020-11-19 Added v4 PCB
2020-11-19 silkscreen cleanup
2020-11-19 add i2c resistors, cleanups
2020-11-22 more tweaks
2020-12-16 cleanups
2020-12-31 yet more cleanups
2021-01-03 ye more cleanups
2021-01-06 more tidyups
2021-01-14 3D stuff
2021-01-15 3D packages
2021-01-22 Started adding level translators
2021-01-22 added note
2021-01-26 More notes
2021-01-31 different level translators
2021-01-31 notes
2021-02-08 another different level converter, routing
2021-02-14 data line series resistors, separate enables for clk/lat, updated ioc file
2021-02-16 Pin reshuffle for proto
2021-02-16 more port shuffling
2021-02-16 more pin shuffling
2021-02-17 Buffer reset and per-console setup routines
2021-02-17 N64 buffered open drain support
2021-02-27 Disabled D2 for test purposes
2021-03-04 over/underread
2021-03-07 more new buffers
2021-03-07 more overread stuff
2021-03-07 bleh updates
2021-03-07 over/underread stats
2021-03-08 more code work
2021-03-11 caps
2021-03-15 code for new new new buffers
2021-03-17 new new new new buffers
2021-03-21 new buffer funtimes
2021-03-28 no airwires!
2021-03-28 v4 r2 silkscreen cleanup, combi vis board
2021-03-29 more silkscreen cleanup
2021-03-29 yet more silkscreen cleanup
2021-03-29 spacing out components
2021-03-31 more tidying
2021-04-02 ground fill on top
2021-04-02 rerouted vis board, rev2 cleanups
2021-04-05 more board tidyups
2021-05-09 part number updates
2021-05-14 code for v4r2 PCB
2021-06-01 more work on code
2021-06-03 v3/v4 board work
2021-06-07 fixed OLED pinout
2021-06-08 bleh
2021-06-08 3D parts

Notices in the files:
parts and their libraries:
SparkFun-Connectors: Licensing: CC v3.0 Share-Alike You are welcome to use this library for commercial purposes.
